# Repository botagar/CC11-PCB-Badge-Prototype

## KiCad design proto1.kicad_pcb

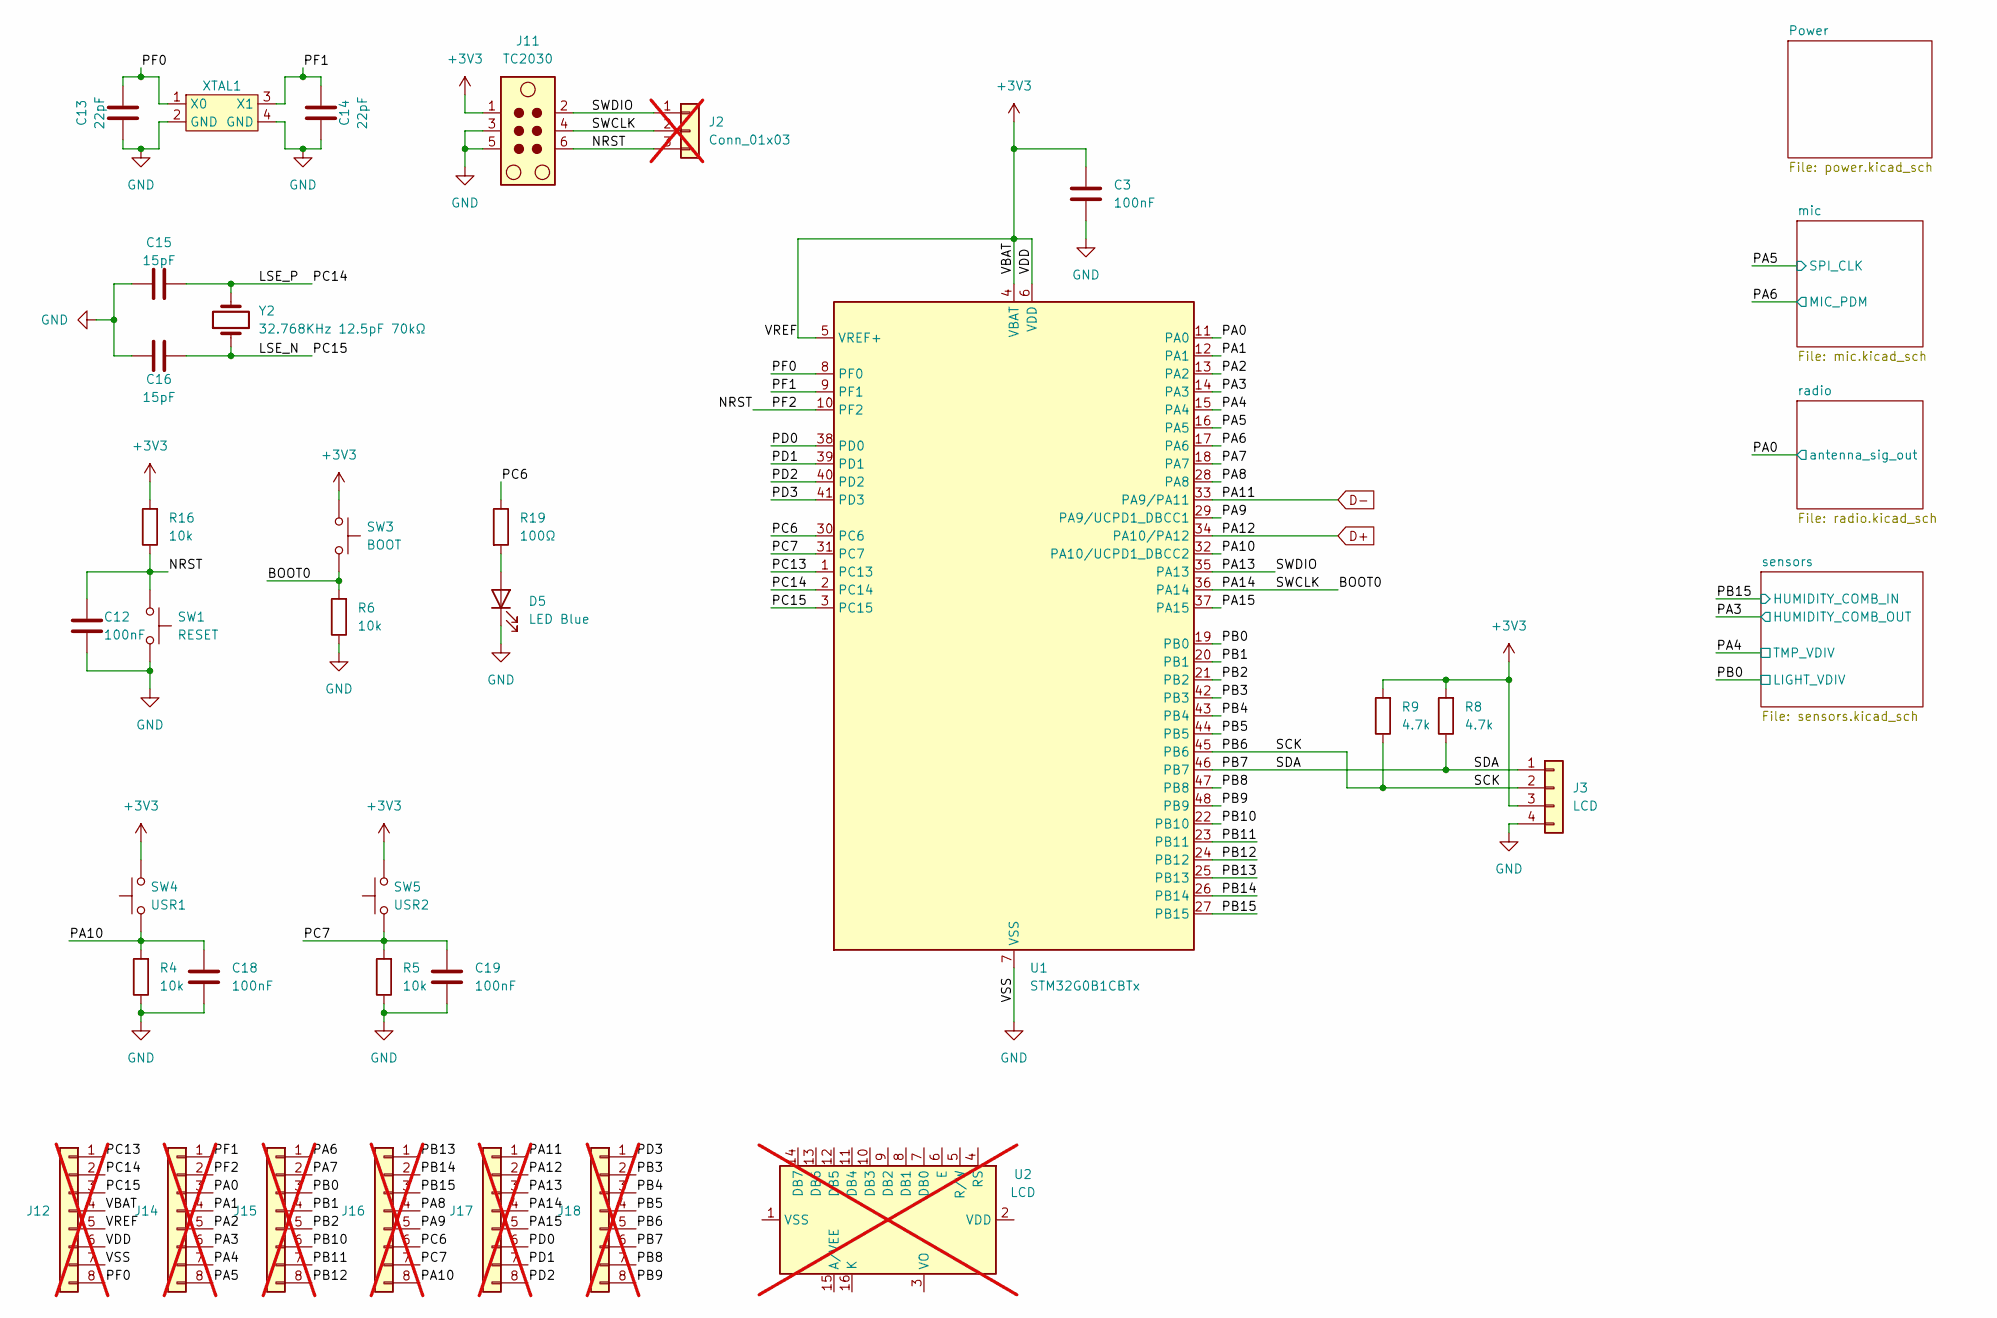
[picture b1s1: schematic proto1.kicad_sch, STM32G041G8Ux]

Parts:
C3, C12, C18, C19: 100nF; C_0402_1005Metric; Part No CGA0402X7R104K6R3GT
C13, C14: 22pF; C_0402_1005Metric_Pad0.74x0.62mm_HandSolder; Part No CGA0402C0G220J500GT
C15, C16: 15pF; C_0402_1005Metric; Part No CGA0402C0G150J500GT
D5: LED Blue; LED_0603_1608Metric; Part No GL0603UB01
J2: Conn_01x03; PinHeader_1x03_P2.54mm_Vertical; not fitted
J3: LCD; PinSocket_1x04_P2.54mm_Vertical_SMD_Pin1Left; Part No F136-1104S3CMUB2
J11: TC2030; Tag-Connect_TC2030-IDC-NL_2x03_P1.27mm_Vertical
J12, J14, J15, J16, J17, J18: PA_L; PinSocket_1x08_P1.27mm_Vertical_SMD_Pin1Left; Part No HX PM1.27-1x8P TP-YQ; not fitted
R4, R5, R6, R16: 10k; R_0402_1005Metric; Part No SCR0402J10K
R8, R9: 4.7k; R_0402_1005Metric; Part No FRC0402J472 TS
R19: 100Ω; R_0402_1005Metric; Part No SCR0402J100R
SW1: RESET; TS110926045; Part No TS110926045
SW3: BOOT; TS110926045; Part No TS110926045
SW4: USR1; TS110926045; Part No TS110926045
SW5: USR2; TS110926045; Part No TS110926045
U1: STM32G0B1CBTx; LQFP-48_7x7mm_P0.5mm; Part No STM32G0B1CBT6
U2: LCD; RC1602A; not fitted
XTAL1: 8Mz CL=20pF; TX32258M4LBDE2T; Part No TX32258M4LBDE2T
Y2: 32.768KHz 12.5pF 70kΩ; Crystal_SMD_EuroQuartz_EQ161-2Pin_3.2x1.5mm; Part No 3K32.768XQ

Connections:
+3V3: C3.1, J3.3, J11.1, J12.4, J12.5, J12.6, R8.2, R9.2, R16.2, SW3.1, SW4.2, SW5.2, U1.4 (VBAT), U1.5 (VREF+), U1.6 (VDD); also elsewhere on the board
/BOOT0: J2.2, J11.4, J17.4, R6.2, SW3.2, U1.36 (PA14)
/LSE_N: C16.2, J12.3, U1.3 (PC15), Y2.1
/LSE_P: C15.2, J12.2, U1.2 (PC14), Y2.2
/NRST: C12.1, J2.3, J11.6, J14.2, R16.1, SW1.1, U1.10 (PF2)
/PA0: J14.3, U1.11 (PA0); also elsewhere on the board
/PA1: J14.4, U1.12 (PA1)
/PA2: J14.5, U1.13 (PA2)
/PA3: J14.6, U1.14 (PA3); also elsewhere on the board
/PA4: J14.7, U1.15 (PA4); also elsewhere on the board
/PA5: J14.8, U1.16 (PA5); also elsewhere on the board
/PA6: J15.1, U1.17 (PA6); also elsewhere on the board
/PA7: J15.2, U1.18 (PA7)
/PA8: J16.4, U1.28 (PA8)
/PA9: J16.5, U1.29 (PA9/UCPD1_DBCC1)
/PA10: C18.1, J16.8, R4.2, SW4.1, U1.32 (PA10/UCPD1_DBCC2)
/PA13: J2.1, J11.2, J17.3, U1.35 (PA13)
/PA15: J17.5, U1.37 (PA15)
/PB0: J15.3, U1.19 (PB0); also elsewhere on the board
/PB1: J15.4, U1.20 (PB1)
/PB2: J15.5, U1.21 (PB2)
/PB3: J18.2, U1.42 (PB3)
/PB4: J18.3, U1.43 (PB4)
/PB5: J18.4, U1.44 (PB5)
/PB6: J3.2, J18.5, R9.1, U1.45 (PB6)
/PB7: J3.1, J18.6, R8.1, U1.46 (PB7)
/PB8: J18.7, U1.47 (PB8)
/PB9: J18.8, U1.48 (PB9)
/PB10: J15.6, U1.22 (PB10)
/PB11: J15.7, U1.23 (PB11)
/PB12: J15.8, U1.24 (PB12)
/PB13: J16.1, U1.25 (PB13)
/PB14: J16.2, U1.26 (PB14)
/PB15: J16.3, U1.27 (PB15); also elsewhere on the board
/PC6: J16.6, R19.1, U1.30 (PC6)
/PC7: C19.1, J16.7, R5.2, SW5.1, U1.31 (PC7)
/PC13: J12.1, U1.1 (PC13)
/PD0: J17.6, U1.38 (PD0)
/PD1: J17.7, U1.39 (PD1)
/PD2: J17.8, U1.40 (PD2)
/PD3: J18.1, U1.41 (PD3)
/PF0: C13.2, J12.8, U1.8 (PF0), XTAL1.1 (X0)
/PF1: C14.2, J14.1, U1.9 (PF1), XTAL1.3 (X1)
D+: J17.2, U1.34 (PA10/PA12); also elsewhere on the board
D-: J17.1, U1.33 (PA9/PA11); also elsewhere on the board
GND: C3.2, C12.2, C13.1, C14.1, C15.1, C16.1, C18.2, C19.2, D5.1 (K), J3.4, J11.3, J11.5, J12.7, R4.1, R5.1, R6.1, SW1.2, U1.7 (VSS), XTAL1.2 (GND), XTAL1.4 (GND); also elsewhere on the board
unnamed: D5.2 (A), R19.2

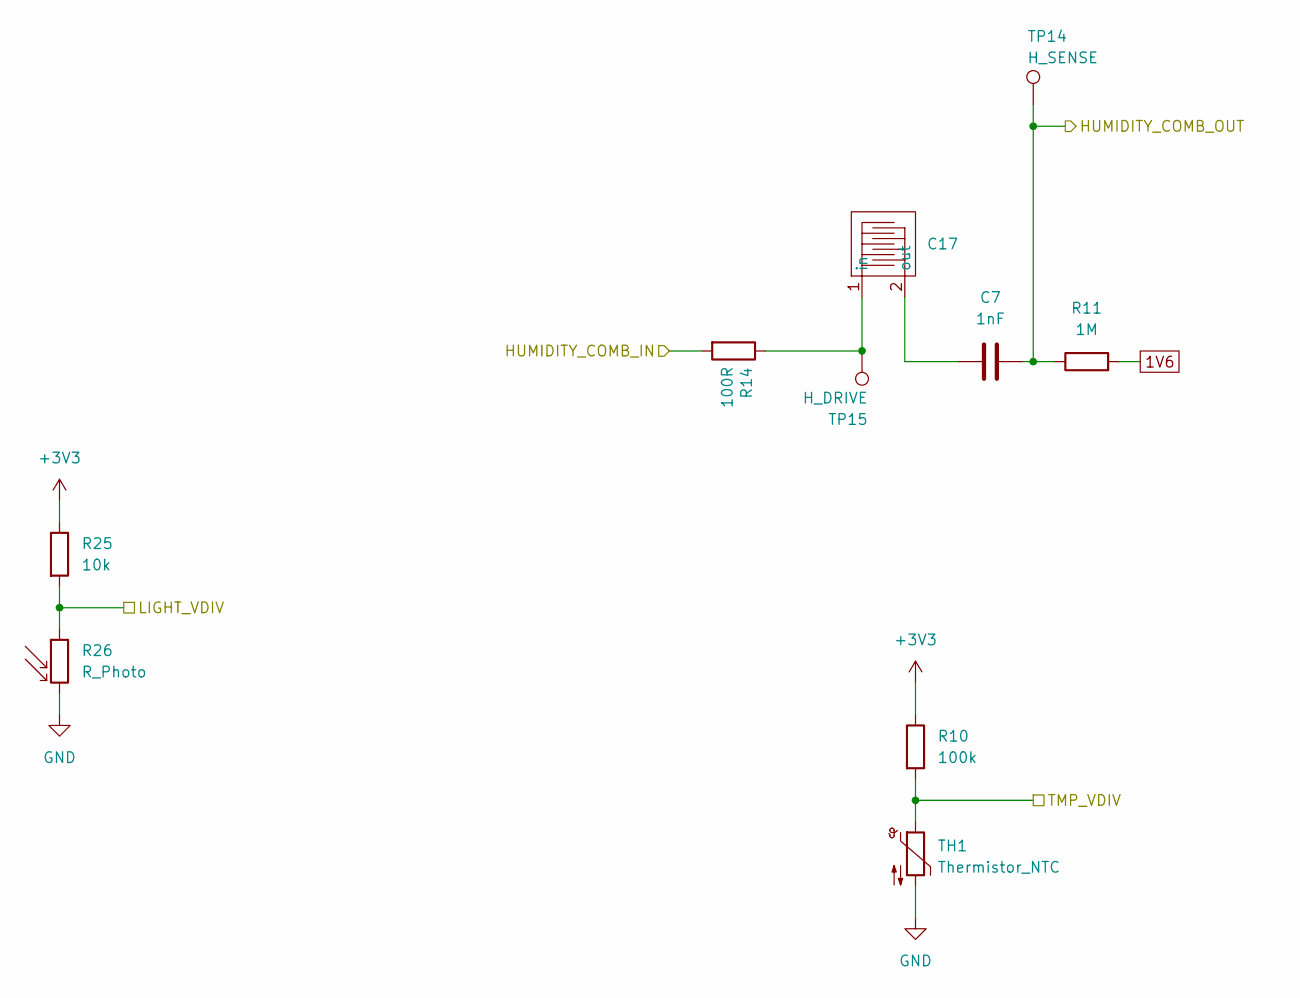
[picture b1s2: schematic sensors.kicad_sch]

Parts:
C7: 1nF; C_0402_1005Metric; Part No CGA0402X7R102M500GT
C17: single_layer_comb_34T
R10: 100k; R_0402_1005Metric; Part No FRC0402J104 TS
R11: 1M; R_0402_1005Metric; Part No FRC0402J105 TS
R14: 100R; R_0402_1005Metric; Part No SCR0402J100R
R25: 10k; R_0402_1005Metric; Part No SCR0402J10K
R26: R_Photo; SMD_3.6x2.4mm; Part No GT36528
TH1: Thermistor_NTC; R_0603_1608Metric; Part No TX06F104F4100ER
TP14: H_SENSE; TestPoint_Pad_D1.5mm
TP15: H_DRIVE; TestPoint_Pad_D1.5mm

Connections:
1V6: R11.2; also elsewhere on the board
+3V3: R10.1, R25.1; also elsewhere on the board
/PA3: C7.2, R11.1, TP14.1; also elsewhere on the board
/PA4: R10.2, TH1.1; also elsewhere on the board
/PB0: R25.2, R26.1; also elsewhere on the board
/PB15: R14.2; also elsewhere on the board
GND: R26.2, TH1.2; also elsewhere on the board
unnamed: C17.1 (in), R14.1, TP15.1
unnamed: C7.1, C17.2 (out)

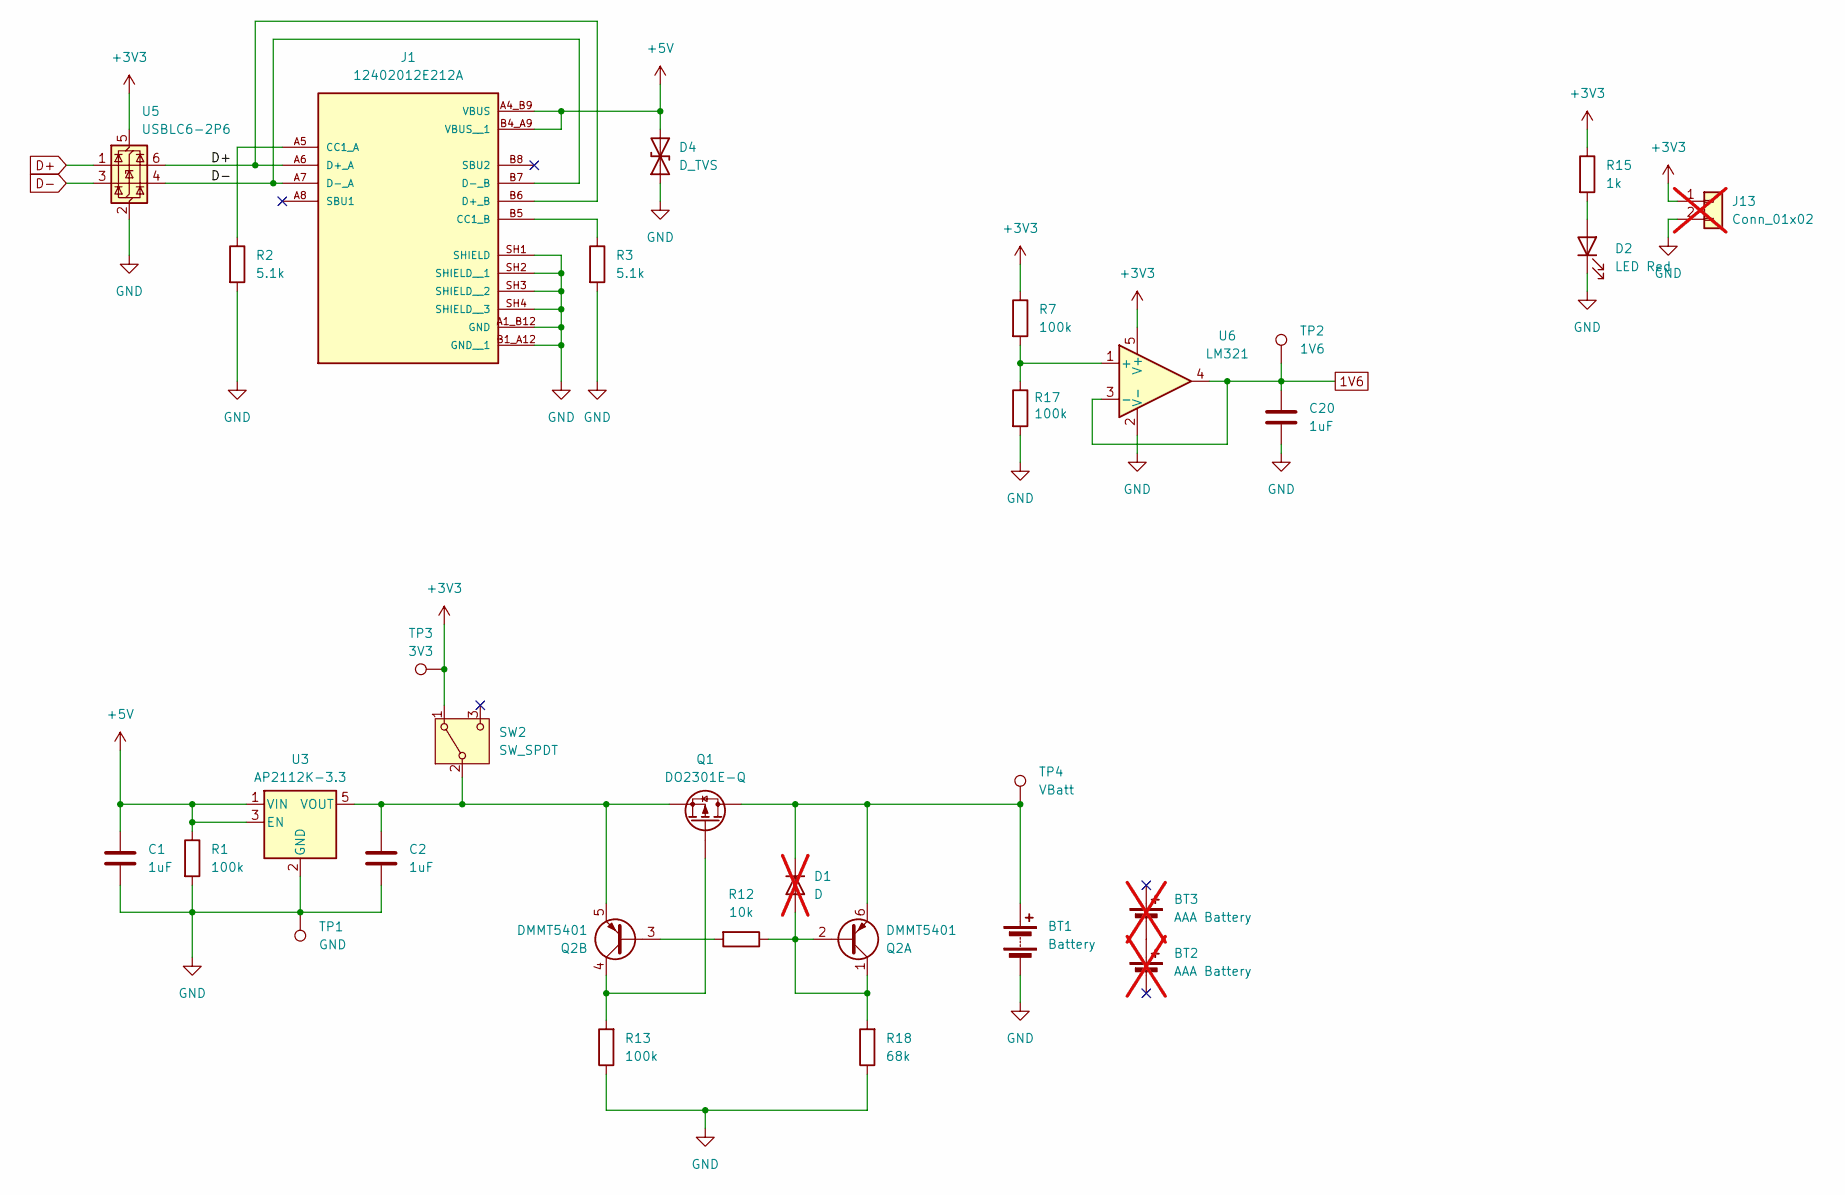
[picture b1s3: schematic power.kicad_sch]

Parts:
BT1: Battery; BatteryHolder_Keystone_2468_2xAAA; Part No BH2AAATH
BT2, BT3: AAA Battery; not fitted
C1, C2, C20: 1uF; C_0402_1005Metric; Part No CGA0402X5R105K100GT
D1: D; D_0402_1005Metric; Part No TPNSR05F30NXT5G; not fitted
D2: LED Red; LED_0603_1608Metric; Part No XL-1608SURC-06
D4: D_TVS; SOD-882; Part No ESD8D5.0CAT5G
J1: 12402012E212A; AMPHENOL_12402012E212A; PARTREV 4
J13: Conn_01x02; PinSocket_1x02_P2.54mm_Vertical; not fitted
Q1: DO2301E-Q; SOT-23; Part No DO2301E-Q
Q2: DMMT5401; SOT-23-6; Part No DMMT5401-7-F
R1, R7, R13, R17: 100k; R_0402_1005Metric; Part No FRC0402J104 TS
R2, R3: 5.1k; R_0402_1005Metric; Part No FRC0402J512 TS
R12: 10k; R_0402_1005Metric; Part No SCR0402J10K
R15: 1k; R_0402_1005Metric; Part No SCR0402J1K
R18: 68k; R_0402_1005Metric; Part No SCR0402J68K
SW2: SW_SPDT; SK12D07VG3; Part No SK12D07VG3
TP1: GND; TestPoint_Pad_1.0x1.0mm
TP2: 1V6; TestPoint_Pad_1.0x1.0mm
TP3: 3V3; TestPoint_Pad_1.0x1.0mm
TP4: VBatt; TestPoint_Pad_1.0x1.0mm
U3: AP2112K-3.3; SOT-23-5; Part No AP2112K-3.3TRG1
U5: USBLC6-2P6; SOT-666; Part No USBLC6-2P6
U6: LM321; SOT-23-5; Part No LMV321

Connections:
1V6: C20.1, TP2.1, U6.3 (-), U6.4; also elsewhere on the board
+3V3: J13.1, R7.1, R15.1, SW2.1 (A), TP3.1, U5.5 (VBUS), U6.5 (V+); also elsewhere on the board
+5V: C1.1, D4.2 (A2), J1.A4_B9 (VBUS), J1.B4_A9 (VBUS__1), R1.1, U3.1 (VIN), U3.3 (EN)
D+: J1.A6 (D+_A), J1.B6 (D+_B), U5.1 (I/O1), U5.6 (I/O1); also elsewhere on the board
D-: J1.A7 (D-_A), J1.B7 (D-_B), U5.3 (I/O2), U5.4 (I/O2); also elsewhere on the board
GND: BT1.2 (-), C1.2, C2.2, C20.2, D2.1 (K), D4.1 (A1), J1.A1_B12 (GND), J1.B1_A12 (GND__1), J1.SH1 (SHIELD), J1.SH2 (SHIELD__1), J1.SH3 (SHIELD__2), J1.SH4 (SHIELD__3), J13.2, R1.2, R2.2, R3.2, R13.1, R17.2, R18.1, TP1.1, U3.2 (GND), U5.2 (GND), U6.2 (V-); also elsewhere on the board
unnamed: BT1.1 (+), D1.1 (K), Q1.3 (D), Q2.6 (E1), TP4.1
unnamed: BT2.1 (+), BT3.2 (-)
unnamed: D1.2 (A), Q2.1 (C1), Q2.2 (B1), R12.1, R18.2
unnamed: D2.2 (A), R15.2
unnamed: J1.A5 (CC1_A), R2.1
unnamed: J1.B5 (CC1_B), R3.1
unnamed: Q1.1 (G), Q2.4 (C2), R13.2
unnamed: C2.1, Q1.2 (S), Q2.5 (E2), SW2.2 (B), U3.5 (VOUT)
unnamed: Q2.3 (B2), R12.2
unnamed: R7.2, R17.1, U6.1 (+)

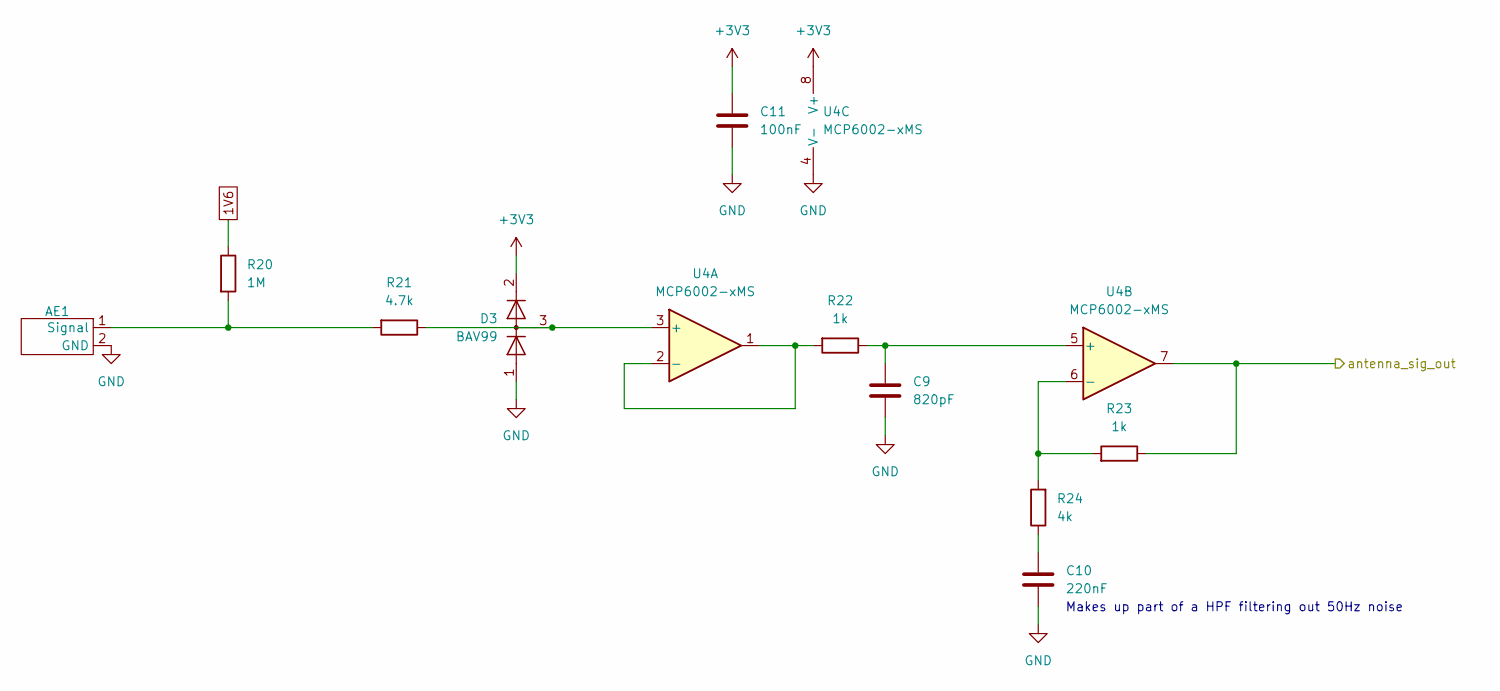
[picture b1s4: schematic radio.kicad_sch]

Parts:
AE1: capacitive_coupled_50mmx8mm
C9: 820pF; C_0402_1005Metric; Part No CGA0402X7R821K500GT
C10: 220nF; C_0402_1005Metric; Part No CGA0402X7R224K160GT
C11: 100nF; C_0402_1005Metric; Part No CGA0402X7R104K6R3GT
D3: BAV99; SOT-23; Part No BAV99
R20: 1M; R_0402_1005Metric; Part No FRC0402J105 TS
R21: 4.7k; R_0402_1005Metric; Part No FRC0402J472 TS
R22, R23: 1k; R_0402_1005Metric; Part No SCR0402J1K
R24: 4k; R_0402_1005Metric; Part No FRC0402F4021TS
U4: MCP6002-xMS; SOP-8_3.76x4.96mm_P1.27mm; Part No MCP6002T-I/SN(LX)

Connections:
1V6: R20.1; also elsewhere on the board
+3V3: C11.1, D3.2 (A), U4.8 (V+); also elsewhere on the board
/PA0: R23.1, U4.7; also elsewhere on the board
GND: AE1.2 (GND), C9.2, C10.2, C11.2, D3.1 (K), U4.4 (V-); also elsewhere on the board
unnamed: AE1.1 (Signal), R20.2, R21.2
unnamed: C10.1, R24.1
unnamed: D3.3 (K), R21.1, U4.3 (+)
unnamed: R22.2, U4.1, U4.2 (-)
unnamed: C9.1, R22.1, U4.5 (+)
unnamed: R23.2, R24.2, U4.6 (-)

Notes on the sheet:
Makes up part of a HPF filtering out 50Hz noise

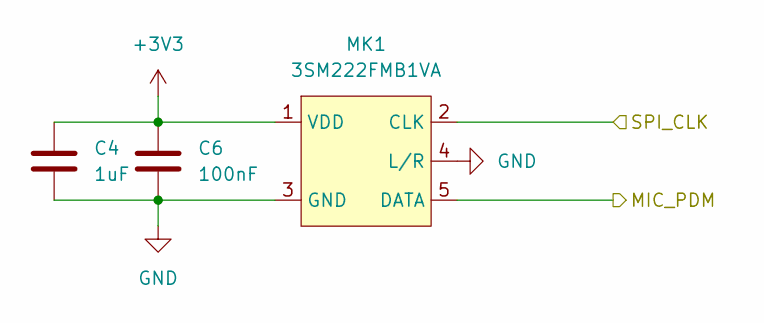
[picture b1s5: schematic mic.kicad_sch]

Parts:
C4: 1uF; C_0402_1005Metric; Part No CGA0402X5R105K100GT
C6: 100nF; C_0402_1005Metric; Part No CGA0402X7R104K6R3GT
MK1: 3SM222FMB1VA; _1; Part No 3SM222FMB1VA

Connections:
+3V3: C4.1, C6.1, MK1.1 (VDD); also elsewhere on the board
/PA5: MK1.2 (CLK); also elsewhere on the board
/PA6: MK1.5 (DATA); also elsewhere on the board
GND: C4.2, C6.2, MK1.3 (GND), MK1.4 (L/R); also elsewhere on the board

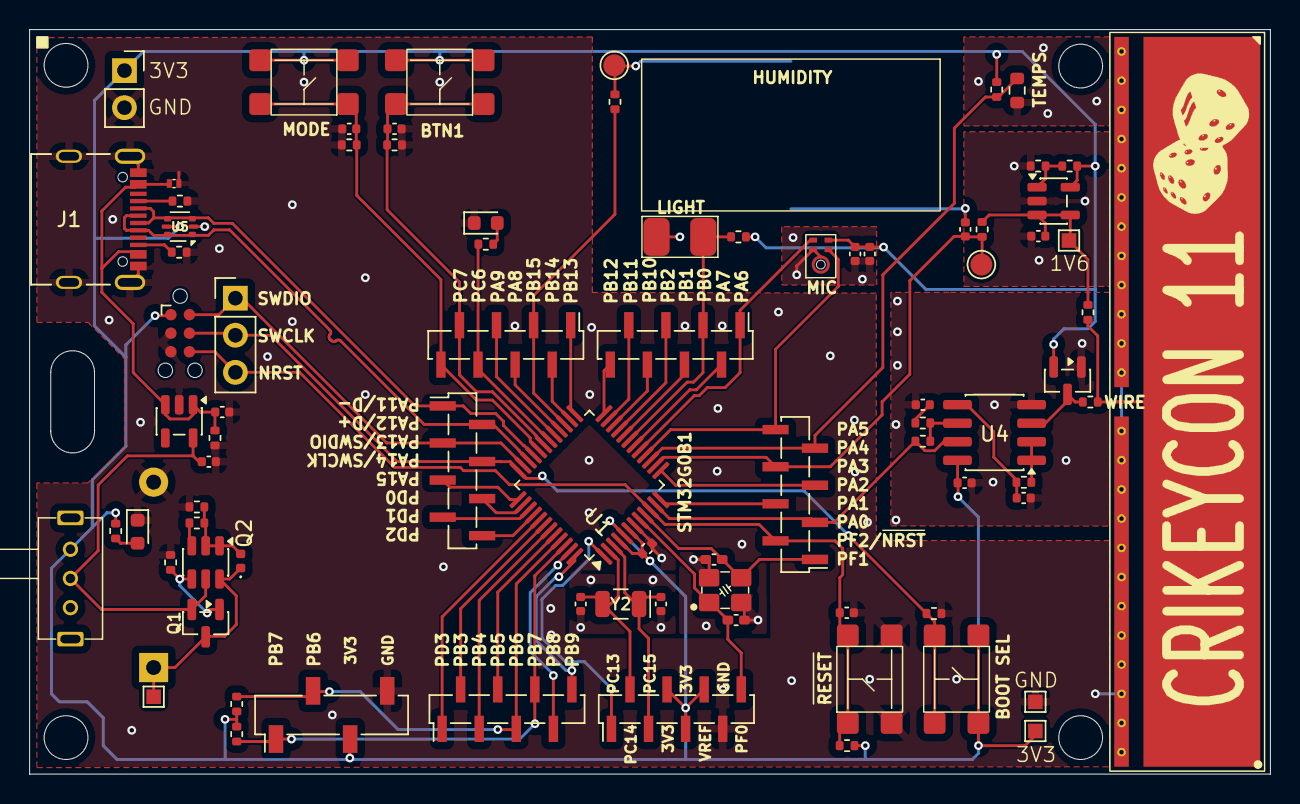
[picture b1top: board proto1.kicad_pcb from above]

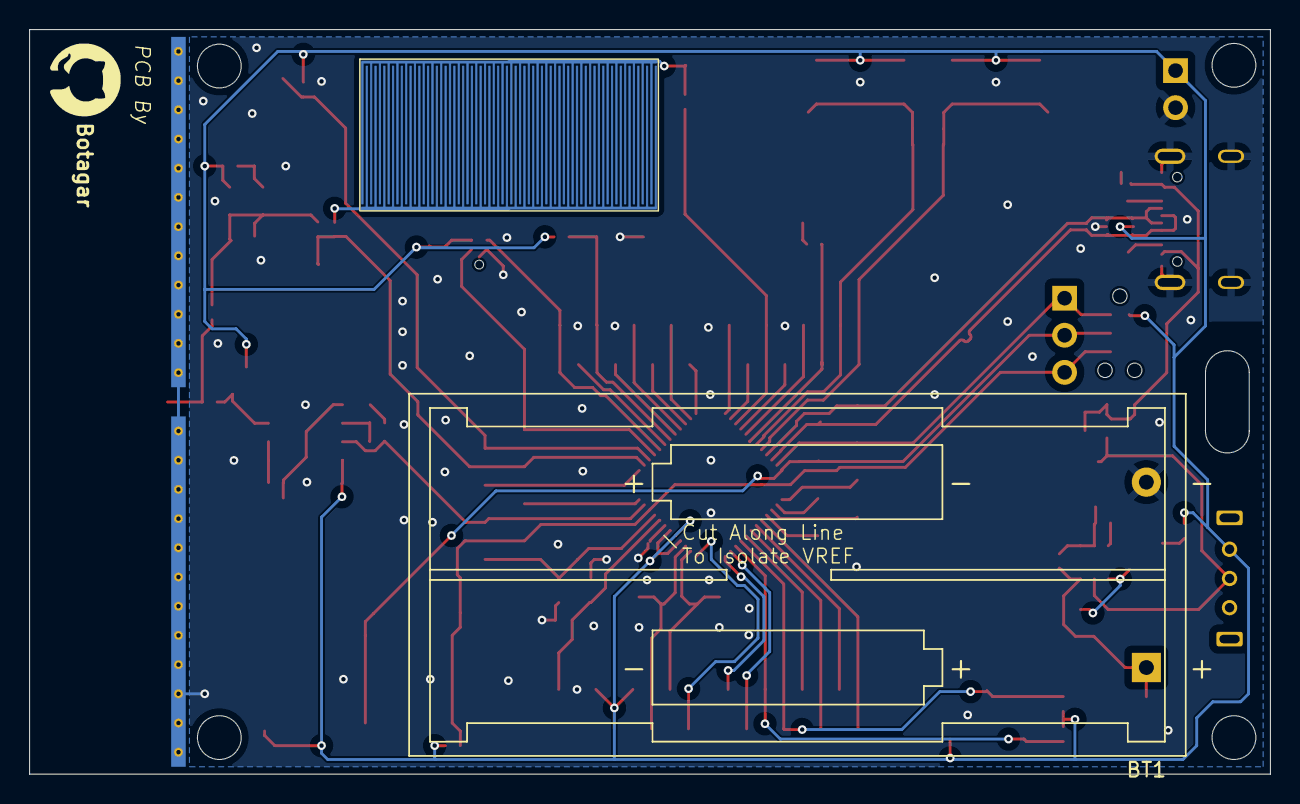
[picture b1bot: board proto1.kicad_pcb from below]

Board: 2 copper layers, 85.0 x 51.0 mm, 84 parts (2 on the bottom side), 66 nets.

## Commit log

2025-12-03 Initial Commit - First prototype
2025-12-06 refactor hierarchical sheets to use sheet pins
2025-12-24 WIP relayout of board
2026-01-19 Board V3
